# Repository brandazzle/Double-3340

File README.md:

# Dual 3340 VCO
This module implements two CEM3340/AS3340 VCO ICs, with front panel pulse width and coarse and fine pitch controls, and linear FM, 1V/octave, switchable hard sync (positive/negative/both), and attenuated PWM inputs.
The 1V/octave inputs are connected to each other via switching jacks, so you can control the pitch of the oscillators simultaneously. (Will need to test for pitch slackening with this.) 
\[This functionality can be customized by soldering only one of the 1V/oct input jacks' switch pins, or removed by soldering neither.\]
All outputs are re-centered and normalized to ±5V. A waveshaping circuit based on [Thomas Henry's VCO-1](https://www.birthofasynth.com/Thomas_Henry/Pages/VCO-1.html) provides a sine output. 
The switchable hard sync uses the hard-sync diode circuit from [the original Curtis Electromusic datasheet.](https://www.curtiselectromusic.com/family-law.html)
The module also implements the chip-to-chip soft synchronization described in the original datasheet, wth front-panel switches for each oscillator. Turning on the switch corresponding to each oscillator causes that oscillator to be synchronized by the other, so you can select sync either way, no sync, or mutual sync.

## Construction
<details><summary>View build instructions</summary>

</details>

## Calibration

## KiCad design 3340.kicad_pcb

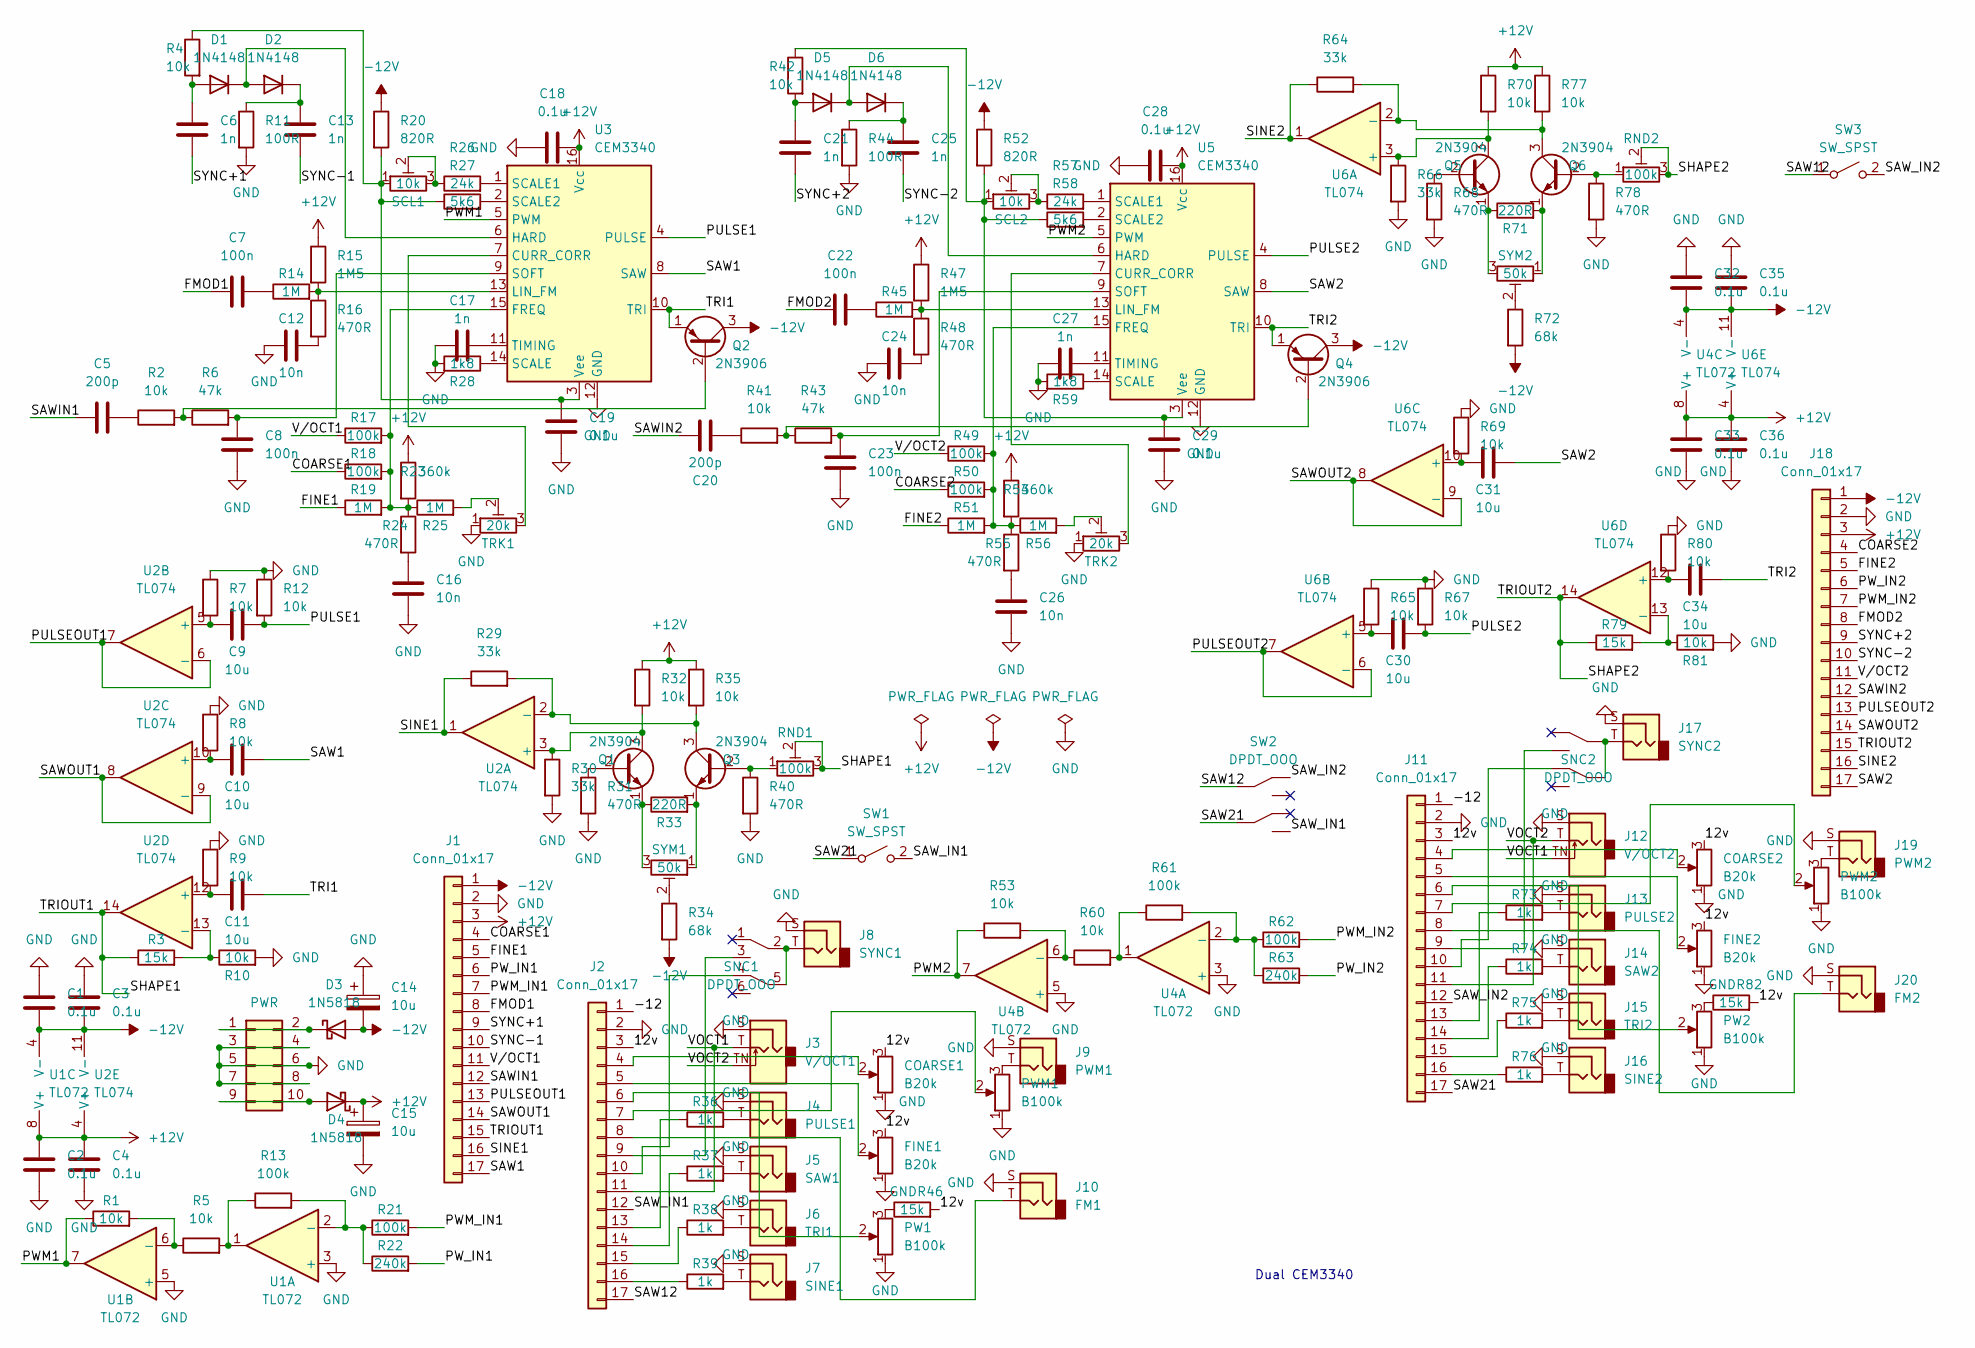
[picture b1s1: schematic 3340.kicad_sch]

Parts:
C1, C2, C3, C4, C18, C19, C28, C29, C32, C33, C35, C36: 0.1u; C_Disc_D3.8mm_W2.6mm_P2.50mm
C5, C20: 200p; C_Disc_D3.8mm_W2.6mm_P2.50mm
C6, C13, C21, C25: 1n; C_Disc_D3.8mm_W2.6mm_P2.50mm
C7, C8, C22, C23: 100n; C_Disc_D3.8mm_W2.6mm_P2.50mm
C9, C10, C11, C30, C31, C34: 10u; C_Disc_D4.3mm_W1.9mm_P5.00mm
C12, C24, C26: 10n; C_Disc_D3.8mm_W2.6mm_P2.50mm
C14, C15: 10u; CP_Radial_D5.0mm_P2.00mm
C16: 10n; C_Disc_D3.0mm_W1.6mm_P2.50mm
C17, C27: 1n; C_Rect_L7.2mm_W5.5mm_P5.00mm_FKS2_FKP2_MKS2_MKP2
COARSE1, COARSE2: B20k; Potentiometer_Alpha_RD901F-40-00D_Single_Vertical_CircularH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
D1, D2, D5, D6: 1N4148; D_DO-35_SOD27_P7.62mm_Horizontal
D3, D4: 1N5818; D_DO-41_SOD81_P10.16mm_Horizontal
FINE1, FINE2: B20k; Potentiometer_Alpha_RD901F-40-00D_Single_Vertical_CircularH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
J1, J2, J11, J18: Conn_01x17; PinHeader_1x17_P2.54mm_Vertical
J3: V/OCT1; Jack_3.5mm_QingPu_WQP-PJ398SM_Vertical_CircularHoles
J4: PULSE1; Jack_3.5mm_QingPu_WQP-PJ398SM_Vertical_CircularHoles
J5: SAW1; Jack_3.5mm_QingPu_WQP-PJ398SM_Vertical_CircularHoles
J6: TRI1; Jack_3.5mm_QingPu_WQP-PJ398SM_Vertical_CircularHoles
J7: SINE1; Jack_3.5mm_QingPu_WQP-PJ398SM_Vertical_CircularHoles
J8: SYNC1; Jack_3.5mm_QingPu_WQP-PJ398SM_Vertical_CircularHoles
J9: PWM1; Jack_3.5mm_QingPu_WQP-PJ398SM_Vertical_CircularHoles
J10: FM1; Jack_3.5mm_QingPu_WQP-PJ398SM_Vertical_CircularHoles
J12: V/OCT2; Jack_3.5mm_QingPu_WQP-PJ398SM_Vertical_CircularHoles
J13: PULSE2; Jack_3.5mm_QingPu_WQP-PJ398SM_Vertical_CircularHoles
J14: SAW2; Jack_3.5mm_QingPu_WQP-PJ398SM_Vertical_CircularHoles
J15: TRI2; Jack_3.5mm_QingPu_WQP-PJ398SM_Vertical_CircularHoles
J16: SINE2; Jack_3.5mm_QingPu_WQP-PJ398SM_Vertical_CircularHoles
J17: SYNC2; Jack_3.5mm_QingPu_WQP-PJ398SM_Vertical_CircularHoles
J19: PWM2; Jack_3.5mm_QingPu_WQP-PJ398SM_Vertical_CircularHoles
J20: FM2; Jack_3.5mm_QingPu_WQP-PJ398SM_Vertical_CircularHoles
PW1, PW2: B100k; Potentiometer_Alpha_RD901F-40-00D_Single_Vertical_CircularH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
PWM1, PWM2: B100k; Potentiometer_Alpha_RD901F-40-00D_Single_Vertical_CircularH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
PWR1: PWR; IDC-Header_2x05_P2.54mm_Vertical
Q1, Q3, Q5, Q6: 2N3904; TO-92_Inline
Q2, Q4: 2N3906; TO-92_Inline
R1, R2, R4, R5, R7, R8, R9, R10, R12, R32, R35, R41, R42, R53, R60, R65, R67, R69, R70, R77, R80, R81: 10k; R_Axial_DIN0207_L6.3mm_D2.5mm_P10.16mm_Horizontal
R3, R46, R79, R82: 15k; R_Axial_DIN0207_L6.3mm_D2.5mm_P10.16mm_Horizontal
R6, R43: 47k; R_Axial_DIN0207_L6.3mm_D2.5mm_P10.16mm_Horizontal
R11, R44: 100R; R_Axial_DIN0207_L6.3mm_D2.5mm_P10.16mm_Horizontal
R13, R17, R18, R21, R49, R50, R61, R62: 100k; R_Axial_DIN0207_L6.3mm_D2.5mm_P10.16mm_Horizontal
R14, R19, R25, R45, R51, R56: 1M; R_Axial_DIN0207_L6.3mm_D2.5mm_P10.16mm_Horizontal
R15, R47: 1M5; R_Axial_DIN0207_L6.3mm_D2.5mm_P10.16mm_Horizontal
R16, R24, R31, R40, R48, R55, R68, R78: 470R; R_Axial_DIN0207_L6.3mm_D2.5mm_P10.16mm_Horizontal
R20, R52: 820R; R_Axial_DIN0207_L6.3mm_D2.5mm_P10.16mm_Horizontal
R22, R63: 240k; R_Axial_DIN0207_L6.3mm_D2.5mm_P10.16mm_Horizontal
R23, R54: 360k; R_Axial_DIN0207_L6.3mm_D2.5mm_P10.16mm_Horizontal
R26, R57: 24k; R_Axial_DIN0207_L6.3mm_D2.5mm_P10.16mm_Horizontal
R27, R58: 5k6; R_Axial_DIN0207_L6.3mm_D2.5mm_P10.16mm_Horizontal
R28, R59: 1k8; R_Axial_DIN0207_L6.3mm_D2.5mm_P10.16mm_Horizontal
R29, R30, R64, R66: 33k; R_Axial_DIN0207_L6.3mm_D2.5mm_P10.16mm_Horizontal
R33, R71: 220R; R_Axial_DIN0207_L6.3mm_D2.5mm_P10.16mm_Horizontal
R34, R72: 68k; R_Axial_DIN0207_L6.3mm_D2.5mm_P10.16mm_Horizontal
R36, R37, R38, R39, R73, R74, R75, R76: 1k; R_Axial_DIN0207_L6.3mm_D2.5mm_P10.16mm_Horizontal
RND1, RND2: 100k; Potentiometer_Bourns_3296W_Vertical
SCL1, SCL2: 10k; Potentiometer_Bourns_3296W_Vertical
SNC1, SNC2: DPDT_OOO; SW_DPDT_Toggle_Miniature_Lug
SW1, SW3: SW_SPST; SW_SPST_Toggle_Subminiature
SW2: DPDT_OOO; SW_DPDT_Toggle_Miniature_Lug
SYM1, SYM2: 50k; Potentiometer_Bourns_3296W_Vertical
TRK1, TRK2: 20k; Potentiometer_Bourns_3296W_Vertical
U1, U4: TL072; DIP-8_W7.62mm_Socket_LongPads
U2, U6: TL074; DIP-14_W7.62mm_Socket_LongPads
U3, U5: CEM3340; DIP-16_W7.62mm_Socket_LongPads

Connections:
+12V: C2.1, C4.1, C15.1, C18.2, C28.2, C33.1, C36.1, D4.1 (K), J1.3, J18.3, R15.1, R23.1, R32.1, R35.1, R47.1, R54.1, R70.1, R77.1, U1.8 (V+), U2.4 (V+), U3.16 (Vcc), U4.8 (V+), U5.16 (Vcc), U6.4 (V+)
-12V: C1.2, C3.2, C14.2, C32.2, C35.2, D3.2 (A), J1.1, J18.1, Q2.3 (C), Q4.3 (C), R20.1, R34.2, R52.1, R72.2, U1.4 (V-), U2.11 (V-), U4.4 (V-), U6.11 (V-)
/12v: COARSE1.3, COARSE2.3, FINE1.3, FINE2.3, J2.3, J11.3, R46.2, R82.2
/-12: J2.1, J11.1
/COARSE1: J1.4, R18.1
/COARSE2: J18.4, R50.1
/FINE1: J1.5, R19.1
/FINE2: J18.5, R51.1
/FMOD1: C7.1, J1.8
/FMOD2: C22.1, J18.8
/PULSE1: C9.2, R12.2, U3.4 (PULSE)
/PULSE2: C30.2, R67.2, U5.4 (PULSE)
/PULSEOUT1: J1.13, U2.6 (-), U2.7
/PULSEOUT2: J18.13, U6.6 (-), U6.7
/PWM1: R1.1, U1.7, U3.5 (PWM)
/PWM2: R53.1, U4.7, U5.5 (PWM)
/PWM_IN1: J1.7, R21.2
/PWM_IN2: J18.7, R62.2
/PW_IN1: J1.6, R22.2
/PW_IN2: J18.6, R63.2
/SAW1: C10.2, J1.17, U3.8 (SAW)
/SAW2: C31.2, J18.17, U5.8 (SAW)
/SAW12: J2.17, SW2.2, SW3.1 (A)
/SAW21: J11.17, SW1.1 (A), SW2.5
/SAWIN1: C5.1, J1.12
/SAWIN2: C20.1, J18.12
/SAWOUT1: J1.14, U2.8, U2.9 (-)
/SAWOUT2: J18.14, U6.8, U6.9 (-)
/SAW_IN1: J2.12, SW1.2 (B), SW2.6
/SAW_IN2: J11.12, SW2.1, SW3.2 (B)
/SHAPE1: J1.15, R3.1, RND1.2, RND1.3, U2.14
/SHAPE2: J18.15, R79.1, RND2.2, RND2.3, U6.14
/SINE1: J1.16, R29.1, U2.1
/SINE2: J18.16, R64.1, U6.1
/SYNC+1: C6.2, J1.9
/SYNC+2: C21.2, J18.9
/SYNC-1: C13.2, J1.10
/SYNC-2: C25.2, J18.10
/TRI1: C11.2, Q2.1 (E), U3.10 (TRI)
/TRI2: C34.2, Q4.1 (E), U5.10 (TRI)
/VOCT1: J2.11, J3.T, J12.TN
/VOCT2: J3.TN, J11.11, J12.T
/V/OCT1: J1.11, R17.1
/V/OCT2: J18.11, R49.1
GND: C1.1, C2.2, C3.1, C4.2, C8.2, C12.1, C14.1, C15.2, C16.2, C17.1, C18.1, C19.2, C23.2, C24.1, C26.2, C27.1, C28.1, C29.2, C32.1, C33.2, C35.1, C36.2, COARSE1.1, COARSE2.1, FINE1.1, FINE2.1, J1.2, J2.2, J3.S, J4.S, J5.S, J6.S, J7.S, J8.S, J9.S, J10.S, J11.2, J12.S, J13.S, J14.S, J15.S, J16.S, J17.S, J18.2, J19.S, J20.S, PW1.1, PW2.1, PWM1.1, PWM2.1, PWR1.3, PWR1.4, PWR1.5, PWR1.6, PWR1.7, PWR1.8, R7.1, R8.1, R9.1, R10.2, R11.2, R12.1, R28.2, R30.2, R31.2, R40.2, R44.2, R59.2, R65.1, R66.2, R67.1, R68.2, R69.1, R78.2, R80.1, R81.2, TRK1.1, TRK2.1, U1.3 (+), U1.5 (+), U3.12 (GND), U4.3 (+), U4.5 (+), U5.12 (GND)
unnamed: C5.2, R2.1
unnamed: C6.1, D1.2 (A), R4.2
unnamed: C7.2, R14.1
unnamed: C8.1, R6.2, U3.9 (SOFT)
unnamed: C9.1, R7.2, U2.5 (+)
unnamed: C10.1, R8.2, U2.10 (+)
unnamed: C11.1, R9.2, U2.12 (+)
unnamed: C12.2, R16.2
unnamed: C13.1, D2.1 (K), R11.1
unnamed: C16.1, R24.2
unnamed: C17.2, U3.11 (TIMING)
unnamed: C19.1, R4.1, R20.2, R27.1, SCL1.1, U3.3 (Vee)
unnamed: C20.2, R41.1
unnamed: C21.1, D5.2 (A), R42.2
unnamed: C22.2, R45.1
unnamed: C23.1, R43.2, U5.9 (SOFT)
unnamed: C24.2, R48.2
unnamed: C25.1, D6.1 (K), R44.1
unnamed: C26.1, R55.2
unnamed: C27.2, U5.11 (TIMING)
unnamed: C29.1, R42.1, R52.2, R58.1, SCL2.1, U5.3 (Vee)
unnamed: C30.1, R65.2, U6.5 (+)
unnamed: C31.1, R69.2, U6.10 (+)
unnamed: C34.1, R80.2, U6.12 (+)
unnamed: COARSE1.2, J2.4
unnamed: COARSE2.2, J11.4
unnamed: D1.1 (K), D2.2 (A), U3.6 (HARD)
unnamed: D3.1 (K), PWR1.1, PWR1.2
unnamed: D4.2 (A), PWR1.9, PWR1.10
unnamed: D5.1 (K), D6.2 (A), U5.6 (HARD)
unnamed: FINE1.2, J2.5
unnamed: FINE2.2, J11.5
unnamed: J2.6, PW1.2
unnamed: J2.7, PWM1.2
unnamed: J2.9, SNC1.3
unnamed: J2.10, SNC1.4
unnamed: J2.13, R36.1
unnamed: J2.14, R37.1
unnamed: J2.15, R38.1
unnamed: J2.16, R39.1
unnamed: J4.T, R36.2
unnamed: J5.T, R37.2
unnamed: J6.T, R38.2
unnamed: J7.T, R39.2
unnamed: J8.T, SNC1.2, SNC1.5
unnamed: J9.T, PWM1.3
unnamed: J2.8, J10.T
unnamed: J11.6, PW2.2
unnamed: J11.7, PWM2.2
unnamed: J11.8, J20.T
unnamed: J11.9, SNC2.3
unnamed: J11.10, SNC2.4
unnamed: J11.13, R73.1
unnamed: J11.14, R74.1
unnamed: J11.15, R75.1
unnamed: J11.16, R76.1
unnamed: J13.T, R73.2
unnamed: J14.T, R74.2
unnamed: J15.T, R75.2
unnamed: J16.T, R76.2
unnamed: J17.T, SNC2.2, SNC2.5
unnamed: J19.T, PWM2.3
unnamed: PW1.3, R46.1
unnamed: PW2.3, R82.1
unnamed: Q1.1 (E), R33.1, SYM1.3
unnamed: Q1.2 (B), R31.1
unnamed: Q1.3 (C), R30.1, R32.2, U2.3 (+)
unnamed: Q2.2 (B), R2.2, R6.1
unnamed: Q3.1 (E), R33.2, SYM1.1
unnamed: Q3.2 (B), R40.1, RND1.1
unnamed: Q3.3 (C), R29.2, R35.2, U2.2 (-)
unnamed: Q4.2 (B), R41.2, R43.1
unnamed: Q5.1 (E), R71.1, SYM2.3
unnamed: Q5.2 (B), R68.1
unnamed: Q5.3 (C), R66.1, R70.2, U6.3 (+)
unnamed: Q6.1 (E), R71.2, SYM2.1
unnamed: Q6.2 (B), R78.1, RND2.1
unnamed: Q6.3 (C), R64.2, R77.2, U6.2 (-)
unnamed: R1.2, R5.1, U1.6 (-)
unnamed: R3.2, R10.1, U2.13 (-)
unnamed: R5.2, R13.1, U1.1
unnamed: R13.2, R21.1, R22.1, U1.2 (-)
unnamed: R14.2, R15.2, R16.1, U3.13 (LIN_FM)
unnamed: R17.2, R18.2, R19.2, R23.2, R24.1, R25.1, U3.15 (FREQ)
unnamed: R25.2, TRK1.2
unnamed: R26.1, SCL1.2, SCL1.3
unnamed: R26.2, U3.1 (SCALE1)
unnamed: R27.2, U3.2 (SCALE2)
unnamed: R28.1, U3.14 (SCALE)
unnamed: R34.1, SYM1.2
unnamed: R45.2, R47.2, R48.1, U5.13 (LIN_FM)
unnamed: R49.2, R50.2, R51.2, R54.2, R55.1, R56.1, U5.15 (FREQ)
unnamed: R53.2, R60.1, U4.6 (-)
unnamed: R56.2, TRK2.2
unnamed: R57.1, SCL2.2, SCL2.3
unnamed: R57.2, U5.1 (SCALE1)
unnamed: R58.2, U5.2 (SCALE2)
unnamed: R59.1, U5.14 (SCALE)
unnamed: R60.2, R61.1, U4.1
unnamed: R61.2, R62.1, R63.1, U4.2 (-)
unnamed: R72.1, SYM2.2
unnamed: R79.2, R81.1, U6.13 (-)
unnamed: TRK1.3, U3.7 (CURR_CORR)
unnamed: TRK2.3, U5.7 (CURR_CORR)

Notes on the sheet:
Dual CEM3340

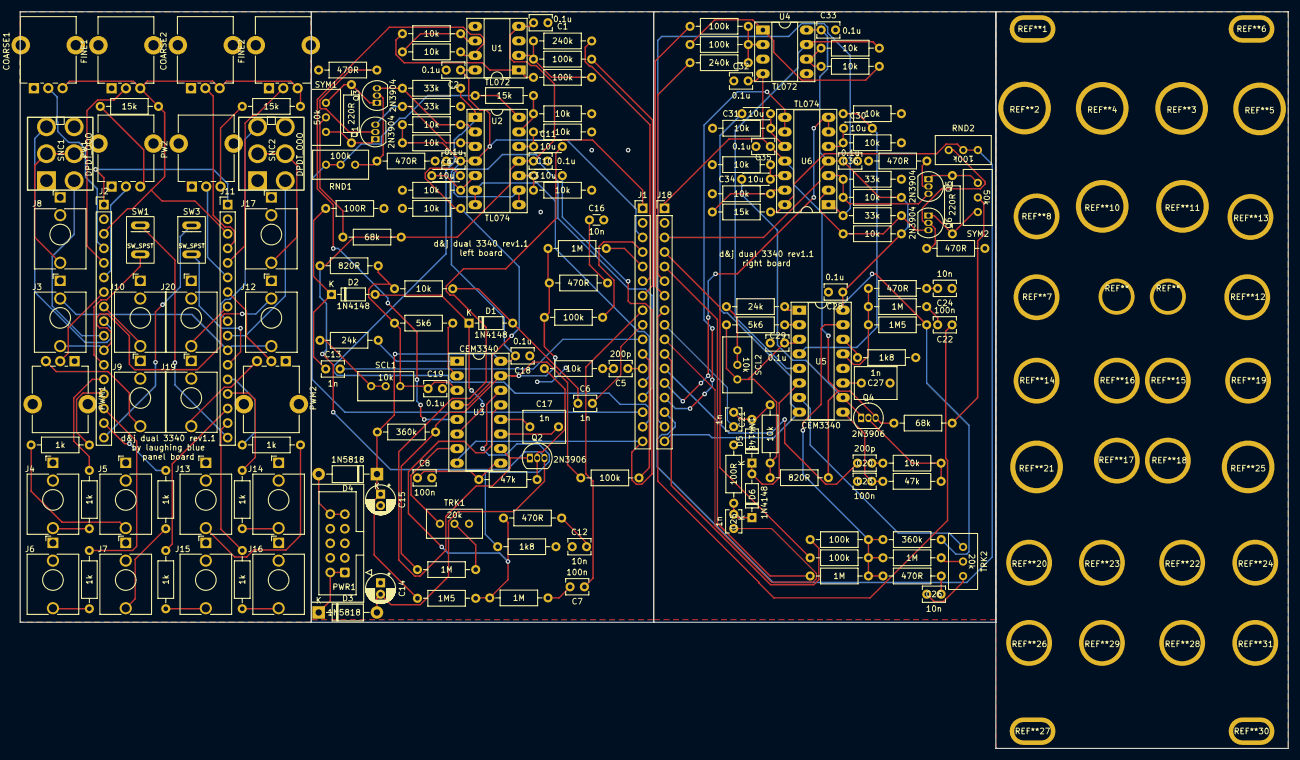
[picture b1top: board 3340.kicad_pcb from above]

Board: 2 copper layers, 221.2 x 128.5 mm, 177 parts (0 on the bottom side), 149 nets.

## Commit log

2022-05-10 Fix power routing
2022-05-10 Add .gitignore
2022-05-10 Test .gitignore
2022-05-10 Update pin header footprints
2022-05-10 Fix synch switches in schematic
2022-05-10 Fix sync switches on board
2022-05-10 Add value labels to potentiometers
2022-05-10 Fix electrolytic footprints
2022-05-10 Start backboard 1
2022-05-10 Use autoplace from here
2022-05-10 Fix PWM2 connection
2022-05-10 Finish backboard 1
2022-05-10 Start backboard 2
2022-05-10 Finish backboard 2
2022-05-10 Fix grid alignment
2022-05-10 Add spacing measurements
2022-05-11 Further comments
2022-05-11 Fix IC labels
2022-05-11 Exclude corner mounts from BOM
2022-05-11 Add panel positions
2022-05-11 Adjust all potentiometers
2022-05-11 Fix various errors
2022-05-11 Adjust panel placements
2022-05-11 Add panel holes
2022-05-11 Fill testing
2022-05-12 Fix switch footprints
2022-05-12 Fixes
2022-05-17 Add independent sync switches
2022-05-23 Update footprints
2022-05-23 Wire new switches
2022-05-24 Mark switch holes
2022-05-24 Add some panel hole nets
2022-05-24 Ground panel holes
2022-05-27 Add new switch mounting holes
2022-05-27 Fix switch footprint flat line placement
2022-05-27 Add panel ground planes
2022-05-28 Add measurements for misalignment fixing
2022-06-09 Add all panel correction measurements
